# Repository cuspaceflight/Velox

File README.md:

# Velox

## Build Instructions

### Setup

ESP-IDF is used so will need to be installed

#### Dependencies
- cmake
- esptool
- esp-idf

#### Window
Install instructions can be found [here](https://docs.espressif.com/projects/esp-idf/en/stable/esp32/get-started/windows-setup.html)

#### Linux
If nix is used then there is a provided flake.nix that will handle all dependencies

## Usage
Run `make menuconfig` to access to configuration options

`make flash` will compile and flash the firmware to the ESP32

`make monitor` will start the monitor to readback any messages from the ESP32

Under "General Settings" there are the options for the web and LoRa configuration.

### Lora
Under the LoRa section it is possible to modify the settings for
- Sync Word
- Frequency
- Spreading Factor
- Bandwidth
- Coding Rate
- Preamble Length
- Implicit Header
- CRC
- Invert IQ

### Web
Under the Web section it is possible to modify the settings for
- SSID
- WiFi Password
- Channel
- Max connections

## Modifying
To modify the ground station to accept other
data then it is only necessary to modify `config.h` and `web_files.h`

`config.h` contains the raw struct that is used
for decoding the received messages. The contents of this
should match what is being sent.

The contents of render_oled represent what will be displayed on the OLED
screen.

format_json is used to display the contents on the web server that is
hosted

`web_files.h` represents the UI of the web server. This
is a `RAWSTRING` that should represent some HTML code.

The code that is featured was used for Panthera, but can be modified for
other rockets. For those rockets, additional branches should be
made to which the changes are commited

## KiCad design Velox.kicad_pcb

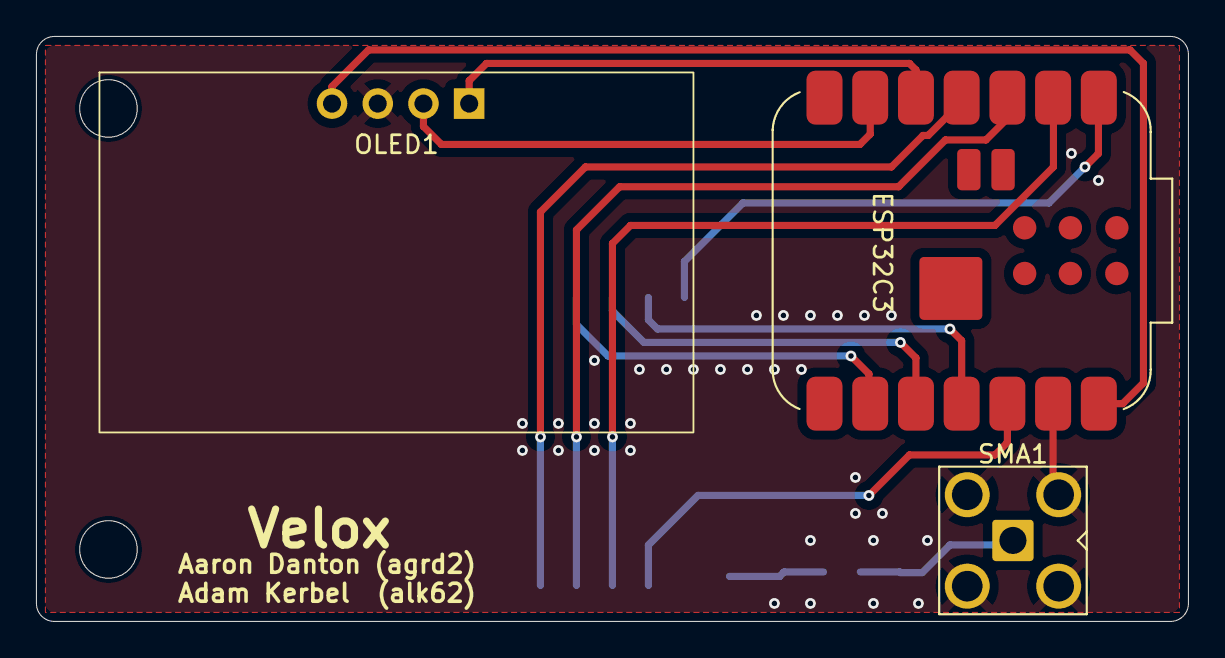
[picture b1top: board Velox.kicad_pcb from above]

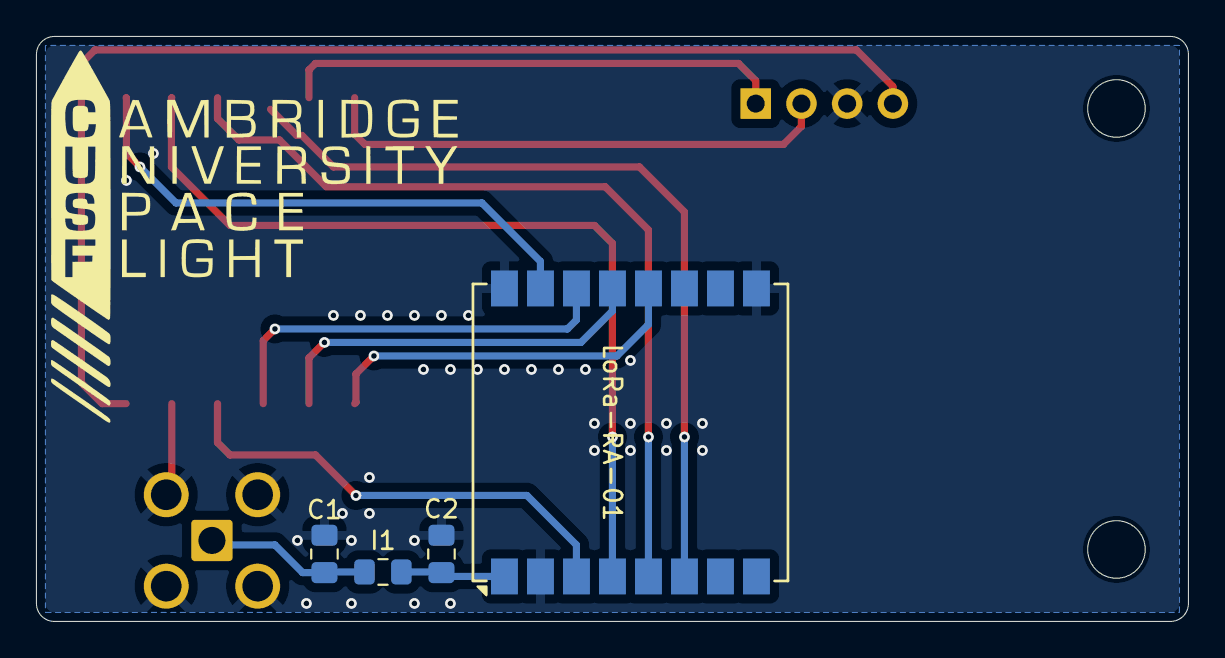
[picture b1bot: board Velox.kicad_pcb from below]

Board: 2 copper layers, 64.0 x 32.5 mm, 7 parts (4 on the bottom side), 14 nets.

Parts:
C1, C2: C; C_0805_2012Metric_Pad1.18x1.45mm_HandSolder
ESP32C3: MOUDLE-SEEEDUINO-XIAO-ESP32C3; MCU_Seeed_ESP32C3
I1: L; L_0805_2012Metric_Pad1.15x1.40mm_HandSolder
LoRa-RA-01: Ai-Thinker-Ra-01; Ai-Thinker-Ra-01-LoRa
OLED1: OLED; Oled
SMA1: Conn_Coaxial; SMA_Amphenol_901-143_Horizontal

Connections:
ANT: C2.1, I1.1, LoRa-RA-01.1 (ANT)
D0: ESP32C3.1 (PA02_A0_D0), LoRa-RA-01.15 (~NSS)
D1: ESP32C3.2 (PA4_A1_D1), LoRa-RA-01.4 (~RESET)
D2: ESP32C3.3 (PA10_A2_D2), LoRa-RA-01.5 (DIO0)
D3: ESP32C3.4 (PA11_A3_D3), LoRa-RA-01.6 (DIO1)
GND: C1.2, C2.2, ESP32C3.13 (GND), LoRa-RA-01.2 (GND), LoRa-RA-01.9 (GND), LoRa-RA-01.16 (GND), OLED1.3 (GND), SMA1.2 (Ext)
MISO: ESP32C3.10 (PA5_A9_D9_MISO), LoRa-RA-01.13 (MISO)
MOSI: ESP32C3.11 (PA6_A10_D10_MOSI), LoRa-RA-01.14 (MOSI)
unnamed: C1.1, I1.2, SMA1.1 (In)
SCK: ESP32C3.9 (PA7_A8_D8_SCK), LoRa-RA-01.12 (SCK)
SCL: ESP32C3.6 (PA9_A5_D5_SCL), OLED1.2 (SCL)
SDA: ESP32C3.5 (PA8_A4_D4_SDA), OLED1.1 (SDA)
VCC_3.3: ESP32C3.12 (3V3), LoRa-RA-01.3 (VDD)
VCC_5V: ESP32C3.14 (5V), OLED1.4 (VCC)

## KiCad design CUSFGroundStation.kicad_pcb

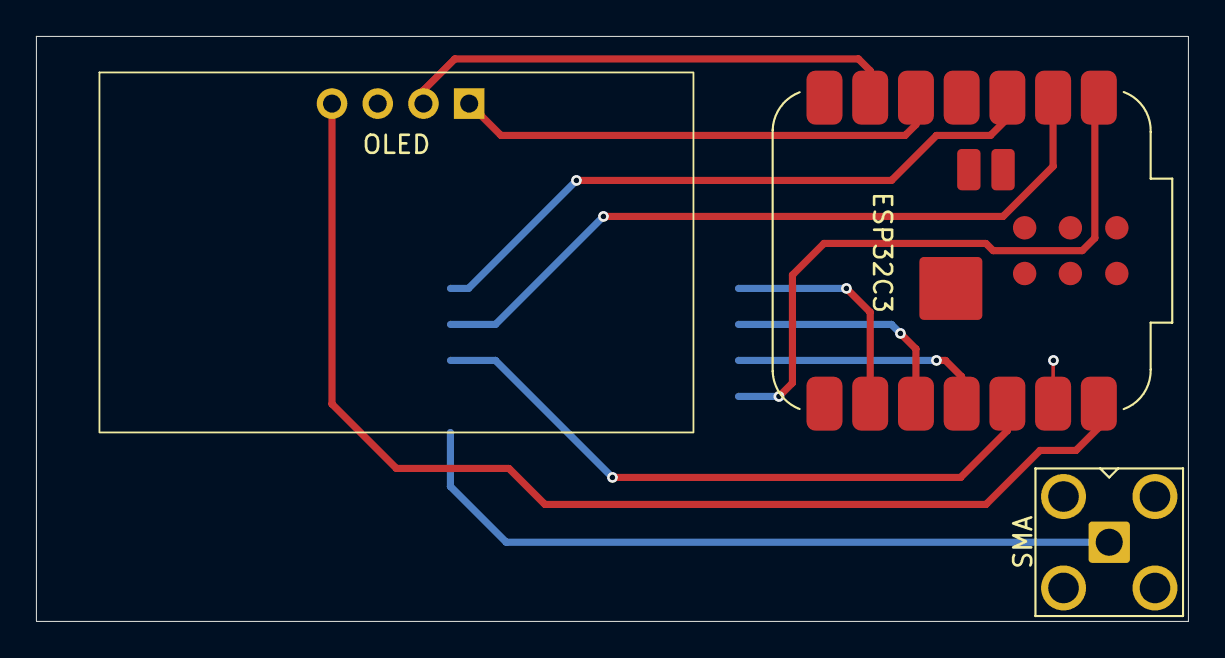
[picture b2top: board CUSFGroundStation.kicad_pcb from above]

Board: 2 copper layers, 64.0 x 32.5 mm, 4 parts (1 on the bottom side), 12 nets.

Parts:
ESP32C3: MOUDLE-SEEEDUINO-XIAO-ESP32C3; MCU_Seeed_ESP32C3
LoRa: Ai-Thinker-Ra-01; Ai-Thinker-Ra-01-LoRa
OLED: OLED; Oled
SMA: Conn_Coaxial; SMA_Amphenol_901-143_Horizontal

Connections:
ANT: LoRa.1 (ANT), SMA.1 (In)
D0: ESP32C3.1 (PA02_A0_D0), LoRa.15 (~NSS)
D1: ESP32C3.2 (PA4_A1_D1), LoRa.4 (~RESET)
D2: ESP32C3.3 (PA10_A2_D2), LoRa.5 (DIO0)
GND: ESP32C3.13 (GND), LoRa.2 (GND), LoRa.9 (GND), LoRa.16 (GND), OLED.3 (GND), SMA.2 (Ext)
MISO: ESP32C3.10 (PA5_A9_D9_MISO), LoRa.13 (MISO)
MOSI: ESP32C3.11 (PA6_A10_D10_MOSI), LoRa.14 (MOSI)
SCK: ESP32C3.9 (PA7_A8_D8_SCK), LoRa.12 (SCK)
SCL: ESP32C3.6 (PA9_A5_D5_SCL), OLED.2 (SCL)
SDA: ESP32C3.5 (PA8_A4_D4_SDA), OLED.1 (SDA)
VCC_3.3: ESP32C3.12 (3V3), LoRa.3 (VDD)
VCC_5V: ESP32C3.14 (5V), OLED.4 (VCC)

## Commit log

2025-07-28 Initial Design
2025-07-29 Changed Project name
2025-07-29 Polished design
2025-07-30 Updated the PCB to feature return vias and some mounting points.
2025-08-06 Basic project
2025-08-06 Makefile to hide idf commands
2025-08-06 Working WiFi example
2025-08-08 Partially working LoRa
2025-08-09 Fixed LoRa. Receive parameters still need to be setup
2025-08-10 Started implementing OLED
2025-08-10 Added more LoRa Commands
2025-08-10 Added Kconfig settings for LoRa
2025-08-11 Split config and handle for oled and lora. Working oled
2025-08-13 Fixed LoRa sync word calculation
2025-08-13 Added font rendering to oled
2025-08-25 Added an easily modifiable config page for future use
2025-09-13 FIX: LoRa receiver working
2025-09-13 Reposition LoRa and oled. Add LoRa defines to separate file
2025-09-13 Moved LoRa defaults to kConfig
2025-09-13 Modified config to work with panthera messages
2025-09-17 Web Setup
2025-09-18 Basic web display of received messages
2025-09-21 Changed how GPS is displayed and possibly fixed RSSI
2026-02-15 Add README.md
2026-02-15 update Kconfig to feature 868MHz instead of 833Mhz
2026-05-03 Config for Leo
2026-05-15 fix: wrong higher frequency set
2026-05-15 feat: add lora sending to library
2026-05-15 fix: log in oled set to info instead of verbose
2026-05-15 feat: add example LoRa sending code
2026-05-21 fix: rssi calculated incorrectly
2026-05-21 fix: lora buffers sized incorrectly for larger messages
2026-05-21 fix: lora buffers sized incorrectly for larger messages
    (cherry picked from commit ec7d0a76bd528367b2ede036740d64bfd90fe9a2)
2026-05-21 feat: configured buffer and config for Lyra board
2026-05-23 feat: update oled and web displays
